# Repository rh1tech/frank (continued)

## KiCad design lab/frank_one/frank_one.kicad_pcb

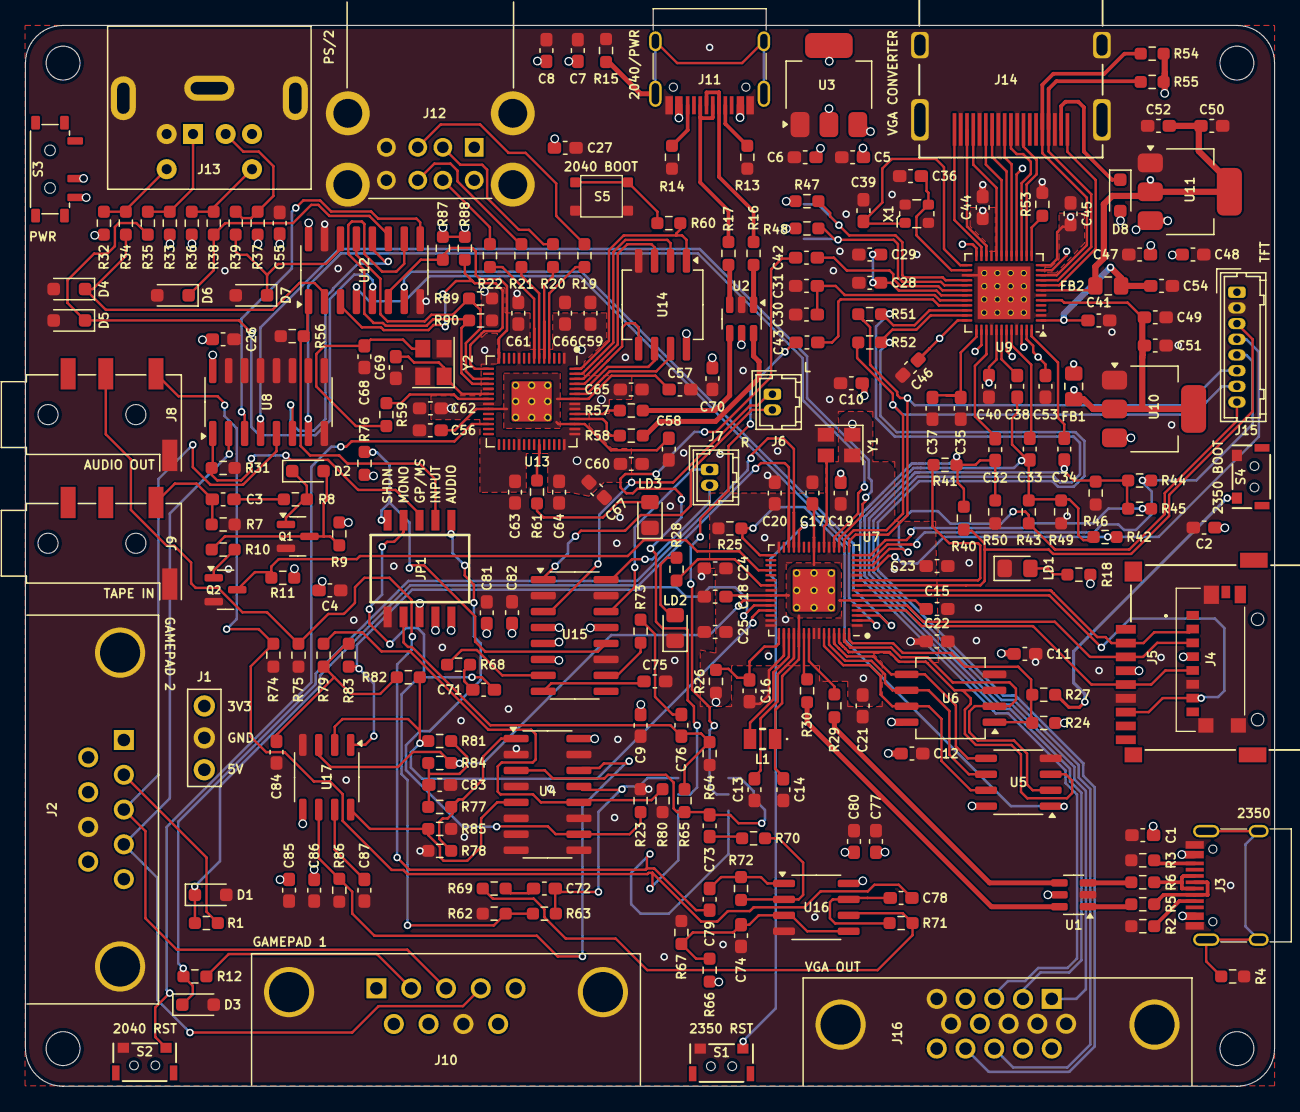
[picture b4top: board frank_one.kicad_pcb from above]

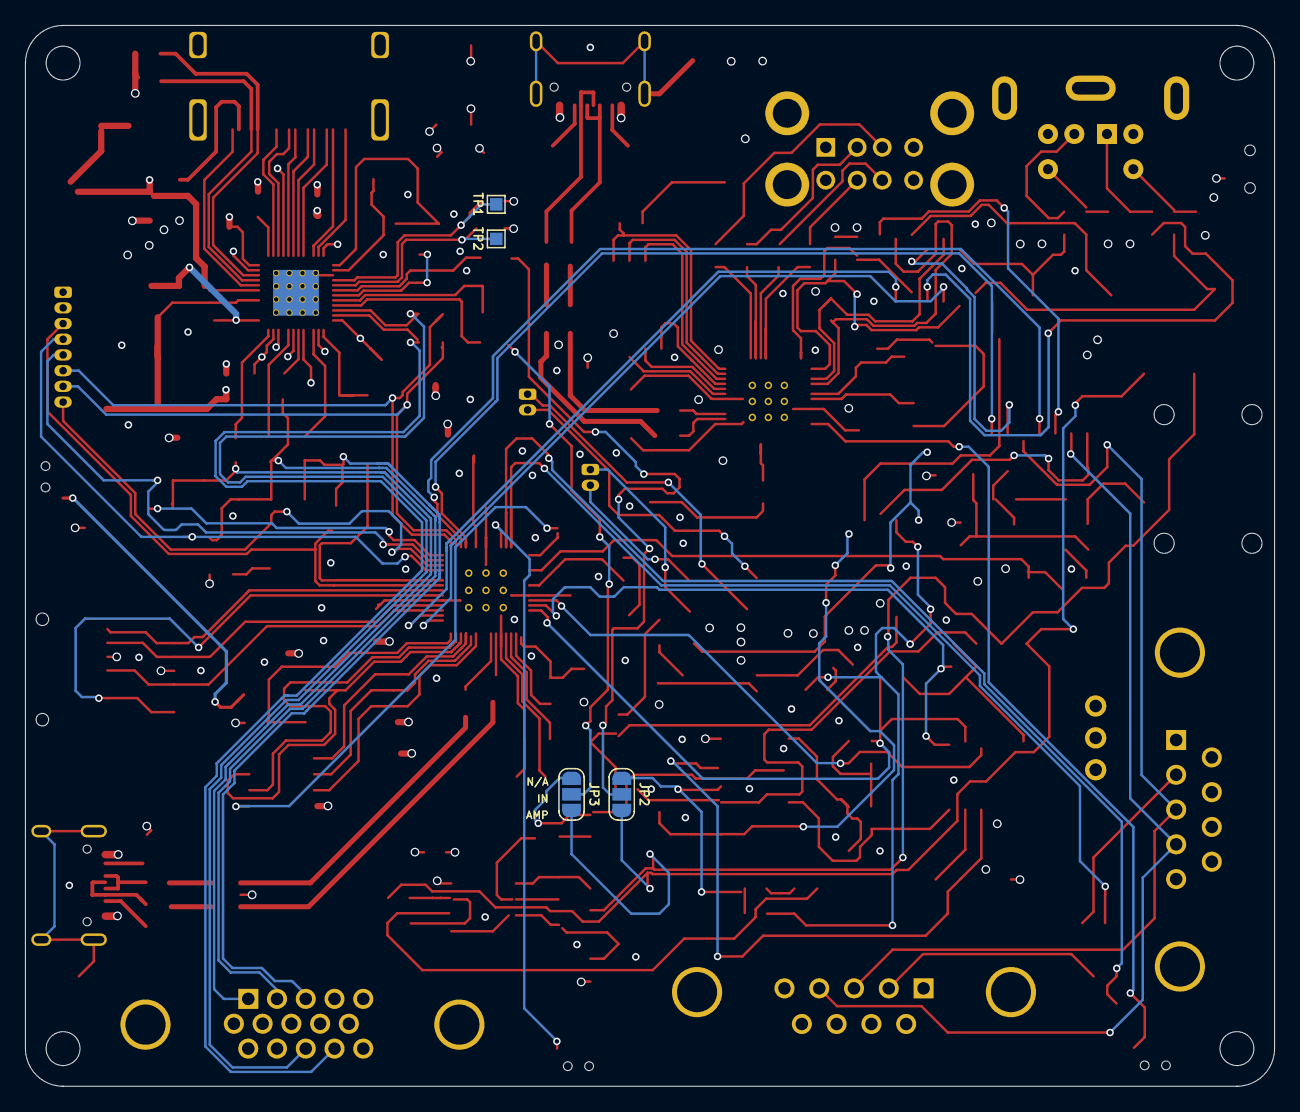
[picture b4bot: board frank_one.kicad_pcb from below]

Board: 4 copper layers, 99.5 x 84.5 mm, 243 parts (4 on the bottom side), 179 nets.

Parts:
C1, C5, C6, C7, C8, C47, C49, C50, C53, C54, C72, C73, C74, C77, C78, C79, C85, C87: 10u; Capacitor (0603)
C2, C3, C4, C9, C10, C11, C12, C15, C18, C19, C20, C21, C22, C23, C24, C25, C26, C27, C32, C33, C34, C40, C41, C44, C45, C46, C48, C55, C56, C57, C59, C61, C62, C63, C64, C65, C66, C67, C70, C75, C80, C86: 100n; Capacitor (0603)
C13, C14, C16, C17, C29, C31, C37: 4.7u; Capacitor (0603)
C28, C30, C35: 220n; Capacitor (0603)
C36, C39, C68, C69: 15p; Capacitor (0603)
C38: 1n; Capacitor (0603)
C42, C43, C51, C52, C58, C60, C71, C76, C81: 1u; Capacitor (0603)
C82: 47u; Capacitor (0603)
C83, C84: 47n; Capacitor (0603)
D1, D3, D4, D5, D6, D7: 3V3; Diode (SOD-323)
D2: 1N4148; Diode (SOD-323)
D8: 1N5819WS; Diode (SOD-323)
FB1, FB2: 220R; Inductor (0805)
H1, H2, H3, H4: MountingHole; Mounting Hole (2.7mm)
J1: PWR; Pin Header (1x03)
J2, J10: D-SUB 9 Male; D-SUB (9 pin, male, top mount)
J3, J11: USB4215-03-A; USB Type C
J4: 0475710001; MicroSD (SMD, short)
J5: 104031-0811; MicroSD (SMD, long)
J6: PAM L; Connector Female 1.25 JST 2P
J7: PAM R; Connector Female 1.25 JST 2P
J8, J9: PJ-320D; Jack (3.5mm, PJ-320D)
J12: SS-52100-004; USB Type A (stacked)
J13: MDC-036; MiniDIN (6 Pin, female)
J14: DC3RX19JA2; HDMI (female)
J15: Pin Header 1x08; Connector Female 1.25 JST 8P
J16: D-SUB 15 Female; D-SUB (15 pin, female)
JP1: Main Jumpers; SMD Switch (5P)
JP2: VGA AUDIO L; Jumper (solder, 3 pins)
JP3: VGA AUDIO R; Jumper (solder, 3 pins)
L1: 3.3u; Inductor (0806)
LD1: Power; LED (0805)
LD2, LD3: Blue; LED (0805)
Q1, Q2: BC850; SOT-23
R1, R11, R12, R18, R27, R28, R32, R33, R36, R37, R53, R59, R60, R61, R83, R84: 1K; Resistor (0603)
R2, R3, R13, R14: 5.1K; Resistor (0603)
R4, R15: 1M; Resistor (0603)
R5, R6, R16, R17, R19, R20, R21, R22: 22R; Resistor (0603)
R7, R34, R35, R38, R39, R51, R52: 100R; Resistor (0603)
R8, R9, R10, R23, R24, R25, R31, R56, R63, R65, R66, R67, R68, R69, R70, R73, R76, R77, R79, R87, R88, R89, R90: 10K; Resistor (0603)
R26: 33R; Resistor (0603)
R29, R30, R57, R58: 27R; Resistor (0603)
R40, R42, R44: 800R; Resistor (0603)
R41, R43, R45: 400R; Resistor (0603)
R46, R49, R50: 75R; Resistor (0603)
R47, R48: 4.7K; Resistor (0603)
R54, R55, R62, R64, R78, R80, R81, R82: 2K; Resistor (0603)
R71, R72: 47K; Resistor (0603)
R74, R75: 20K; Resistor (0603)
R85, R86: 470R; Resistor (0603)
S1, S2: Reset; TACT-SIDE-4623
S3: MSK12C02; Switch (MSK12C02)
S4: TS-1233; TACT-SIDE-4623
S5: Boot 2040; Button (SMD, 3x3mm, 1-1)
TP1: MS9288_SCL; TestPoint (Pad 1.0x1.0mm)
TP2: MS9288_SDA; TestPoint (Pad 1.0x1.0mm)
U1, U2: USBLC6-2SC6; SOT-23-6
U3: NCP1117 3.3; SOT-223
U4: 74HC4052D; SOP-16
U5: ESP-PSRAM32; SO-8
U6: W25Q128JVS; SOIC-8
U7: RP2350; QFN 60 (RP2350A)
U8, U12: SN74CBT3257CDR; SOP-16
U9: MS9288A; QFN 48
U10: AMS1117-3.3; SOT-223
U11: AMS1117-1.8; SOT-223
U13: RP2040; QFN 56
U14: W25Q128JVSIQ; SOIC-8
U15: PAM8403D; SOP-16
U16: LM358; SO-8
U17: TDA1387T; SO-8
X1: 24.576 MHz; Crystal (2520)
Y1: ASE-12MHz; Crystal (3225, active)
Y2: 12 MHz; Crystal (3225)

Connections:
+1V1: C14.1, C15.1, C17.1, C18.1, L1.1, U7.6 (DVDD), U7.23 (DVDD), U7.39 (DVDD), U7.50 (VREG_FB)
+3V3: C2.2, C4.1, C6.1, C9.2, C10.1, C11.1, C12.1, C13.1, C19.1, C20.1, C21.1, C22.1, C23.1, C24.1, C25.1, C59.1, C60.1, C61.1, C62.1, C63.1, C64.1, C65.1, C66.1, C67.1, C70.1, J1.1, J4.P4 (VDD), J5.4 (VDD), R9.1, R11.1, R18.2, R24.1, R25.2, R26.1, R87.2, R88.2, R89.2, R90.2, U3.2 (VO), U4.16 (VCC), U5.8 (VCC), U6.8 (VCC), U7.1 (IOVDD), U7.11 (IOVDD), U7.20 (IOVDD), U7.30 (IOVDD), U7.38 (IOVDD), U7.44 (ADC_AVDD), U7.45 (IOVDD), U7.49 (VREG_VIN), U7.53 (USB_OTP_VDD), U7.54 (QSPI_IOVDD), U13.1 (IOVDD), U13.10 (IOVDD), U13.22 (IOVDD), U13.33 (IOVDD), U13.42 (IOVDD), U13.43 (ADC_AVDD), U13.44 (VREG_IN), U13.48 (USB_VDD), U13.49 (IOVDD), U14.8 (VCC), Y1.1 (EN), Y1.4 (Vdd)
/AMP_IN_L: C72.1, JP2.1, R63.1, U4.13 (1Z)
/AMP_IN_R: C73.1, JP3.1, R65.1, U4.3 (2Z)
/AMP_OUT_L: C78.2, J8.T, JP2.3, R74.2
/AMP_OUT_R: C79.2, J8.R, JP3.3, R75.2
/ASW: JP1.1, R23.2, U4.10 (S0)
/Audio Out/AMP_PAM_OUTL_M: J6.2, U15.3 (-OUTL)
/Audio Out/AMP_PAM_OUTL_P: J6.1, U15.1 (+OUT_L)
/Audio Out/AMP_PAM_OUTR_M: J7.2, U15.14 (-OUT_R)
/Audio Out/AMP_PAM_OUTR_P: J7.1, U15.16 (+OUT_R)
/GP_J3: J2.3, J10.3, U8.5 (2B1)
/GP_J4: J2.4, J10.4, U8.2 (1B1)
/MONO_L: C71.1, JP1.4, R62.1, R63.2
/MONO_R: C76.1, JP1.7, R64.1, R65.2
/MSW: JP1.3, R31.2, U8.1 (S)
/MS_CLK: U8.3 (1B2), U12.9 (3A)
/MS_DATA: U8.6 (2B2), U12.12 (4A)
/PS2/PS2_KB_CLK: J13.5, R32.1, R34.1
/PS2/PS2_KB_DATA: J13.1, R33.1, R35.1
/PS2/PS2_MS_CLK: J13.6, R36.1, R38.1
/PS2/PS2_MS_DATA: J13.2, R37.1, R39.1
/PS2_K_CLK: D4.1 (K), R34.2, U12.2 (1B1)
/PS2_K_DATA: D5.1 (K), R35.2, U12.5 (2B1)
/PS2_M_CLK: D6.1 (K), R38.2, U12.11 (3B1)
/PS2_M_DATA: D7.1 (K), R39.2, U12.14 (4B1)
/PSW: JP1.2, R56.2, U12.1 (S)
/PWM_OUT_L: R79.2, R80.1, U4.12 (1Y0)
/PWM_OUT_R: R77.2, R78.1, U4.1 (2Y0)
/RP1_D+: R29.1, U1.4 (I/O2)
/RP1_D-: R30.1, U1.6 (I/O1)
/RP1_GPIO0: U7.2 (GPIO0), U12.4 (1A)
/RP1_GPIO1: U7.3 (GPIO1), U12.7 (2A)
/RP1_GPIO2: J4.P5 (CLK), J5.5 (CLK), U7.4 (GPIO2)
/RP1_GPIO3: J4.P3 (CMD), J5.3 (CMD), U7.5 (GPIO3)
/RP1_GPIO4: J4.P7 (DAT0), J5.7 (DAT0), U7.7 (GPIO4)
/RP1_GPIO5: J4.P2 (CD/DAT3), J5.2 (DAT3/CD), U7.8 (GPIO5)
/RP1_GPIO6: J15.3, R40.1, U7.9 (GPIO6)
/RP1_GPIO7: R41.1, U7.10 (GPIO7)
/RP1_GPIO8: J15.4, R42.1, U7.12 (GPIO8)
/RP1_GPIO9: J15.8, R43.1, U7.13 (GPIO9)
/RP1_GPIO10: J15.5, R44.1, U7.14 (GPIO10)
/RP1_GPIO11: R45.1, U7.15 (GPIO11)
/RP1_GPIO12: J15.6, R51.1, U7.16 (GPIO12)
/RP1_GPIO13: J15.7, R52.1, U7.17 (GPIO13)
/RP1_GPIO14: U7.18 (GPIO14), U8.4 (1A)
/RP1_GPIO15: U7.19 (GPIO15), U8.7 (2A)
/RP1_GPIO16: D3.1 (K), R12.1, U7.27 (GPIO16)
/RP1_GPIO17: D1.1 (K), R1.1, U7.28 (GPIO17)
/RP1_GPIO19: R25.1, U5.1 (~CE), U7.31 (GPIO19)
/RP1_GPIO22: Q2.3 (C), R11.2, U7.34 (GPIO22)
/RP1_GPIO26: R84.2, U7.40 (GPIO26_ADC0), U17.3 (DATA)
/RP1_GPIO27: R83.2, U7.41 (GPIO27_ADC1), U17.1 (SCLK)
/RP1_GPIO28: R81.1, R82.1, U7.42 (GPIO28_ADC2), U17.2 (LRCK)
/RP1_RUN: S1.1, U7.26 (RUN)
/RP2_D+: R57.1, U2.4 (I/O2)
/RP2_D-: R58.1, U2.6 (I/O1)
/RP2_GPIO2: R19.1, U13.4 (GPIO2)
/RP2_GPIO3: R20.1, U13.5 (GPIO3)
/RP2_GPIO4: R21.1, U13.6 (GPIO4)
/RP2_GPIO5: R22.1, U13.7 (GPIO5)
/RP2_GPIO11: R87.1, U12.6 (2B2), U13.14 (GPIO11)
/RP2_GPIO12: R88.1, U12.3 (1B2), U13.15 (GPIO12)
/RP2_GPIO14: R89.1, U12.13 (4B2), U13.17 (GPIO14)
/RP2_GPIO15: R90.1, U12.10 (3B2), U13.18 (GPIO15)
/RP2_RUN: S2.1, U13.26 (RUN)
/RP2040/GPIO25: R61.2, U13.37 (GPIO25)
/RP2040/QSPI_SCLK: U13.52 (QSPI_SCLK), U14.6 (CLK)
/RP2040/QSPI_SD0: U13.53 (QSPI_SD0), U14.5 (DI(IO0))
/RP2040/QSPI_SD1: U13.55 (QSPI_SD1), U14.2 (DO(IO1))
/RP2040/QSPI_SD2: U13.54 (QSPI_SD2), U14.3 (IO2)
/RP2040/QSPI_SD3: U13.51 (QSPI_SD3), U14.7 (IO3)
/RP2040/QSPI_SS: R60.1, U13.56 (QSPI_SS), U14.1 (~CS)
/RP2040/XIN: C69.1, U13.20 (XIN), Y2.1
/RP2040/XOUT: R59.1, U13.21 (XOUT)
/RP2350A/QSPI_SCLK: U5.6 (SCLK), U6.6 (CLK), U7.56 (QSPI_SCLK)
/RP2350A/QSPI_SD0: U5.5 (SI/SIO), U6.5 (DI(IO0)), U7.57 (QSPI_SD0)
/RP2350A/QSPI_SD1: U5.2 (SO/SIO), U6.2 (DO(IO1)), U7.59 (QSPI_SD1)
/RP2350A/QSPI_SD2: U5.3 (SIO2), U6.3 (IO2), U7.58 (QSPI_SD2)
/RP2350A/QSPI_SD3: U5.7 (SIO3), U6.7 (IO3), U7.55 (QSPI_SD3)
/RP2350A/QSPI_SS: R24.2, R27.1, U6.1 (~CS), U7.60 (QSPI_SS)
/RP2350A/VREG_AVDD: C16.1, R26.2, U7.46 (VREG_AVDD)
/RP2350A/VREG_LX: L1.2, U7.48 (VREG_LX)
/RP2350A/XIN: U7.21 (XIN), Y1.3 (OUT)
/RP2350A/~USB_BOOT: R27.2, S4.2
/SHND: JP1.5, R76.2, U15.12 (SHND)
/TDA_L: R86.2, U4.14 (1Y1), U17.6 (A_LEFT)
/TDA_R: R85.1, U4.5 (2Y1), U17.8 (A_RIGHT)
/VGA/ALIN: C42.1, U9.30 (ALIN)
/VGA/AMS_1V8: C44.1, C50.1, C52.1, FB2.1, U9.7 (AVDD18), U9.16 (AVDD18), U9.21 (AVDD18), U11.2 (VO)
/VGA/AMS_1V8A: C40.1, C41.1, C54.1, FB2.2, U9.1 (AVDD18_ADC), U9.41 (AVDD18_ADC), U9.46 (AVDD18_ADC)
/VGA/AMS_3V3: C46.1, C49.1, C51.1, FB1.2, U9.5 (DVDD33), U9.11 (DVDD33), U9.24 (DVDD33), U9.36 (DVDD33), U10.2 (VO)
/VGA/AMS_3V3A: C45.1, C53.1, FB1.1, U9.12 (AVDD33), U9.38 (AVDD33), U9.43 (AVDD33), U9.47 (AVDD33)
/VGA/ARIN: C43.1, U9.33 (ARIN)
/VGA/B: C32.1, U9.39 (B/Pb)
/VGA/DCCSCL: J14.15 (SCL), R54.1, U9.10 (DCCSCL)
/VGA/DDCSDA: J14.16 (SDA), R55.1, U9.9 (DDCSDA)
/VGA/G: C33.1, U9.44 (G/Y)
/VGA/HPDT: J14.19 (HOT_PLUG_DET), U9.8 (HotPlugDetect)
/VGA/HS: J16.13, R51.2, U9.34 (HSIN)
/VGA/R: C34.1, U9.48 (R/Pr)
/VGA/SCL: R47.1, TP1.1, U9.28 (SCL)
/VGA/SDA: R48.1, TP2.1, U9.29 (SDA)
/VGA/SOG_B: C32.2, J16.3, R40.2, R41.2, R50.1
/VGA/SOG_G: C33.2, C38.2, J16.2, R42.2, R43.2, R49.1
/VGA/SOG_R: C34.2, J16.1, R44.2, R45.2, R46.1
/VGA/TMDS_CLK+: J14.10 (CLKP), U9.15 (TMDS_CLK+)
/VGA/TMDS_CLK-: J14.12 (CLKN), U9.14 (TMDS_CLK-)
/VGA/TMDS_D0+: J14.7 (D0P), U9.18 (TMDS-D0+)
/VGA/TMDS_D0-: J14.9 (D0N), U9.17 (TMDS_D0-)
/VGA/TMDS_D1+: J14.4 (D1P), U9.20 (TMDS_D1+)
/VGA/TMDS_D1-: J14.6 (D1N), U9.19 (TMDS_D1-)
/VGA/TMDS_D2+: J14.1 (D2P), U9.23 (TMDS_D2+)
/VGA/TMDS_D2-: J14.3 (D2N), U9.22 (TMDS_D2-)
/VGA/VS: J16.14, R52.2, U9.35 (VSIN)
/VGA_AIN_L: C42.2, JP2.2
/VGA_AIN_R: C43.2, JP3.2
GND: C1.2, C2.1, C4.2, C5.2, C6.2, C7.2, C8.2, C9.1, C10.2, C11.2, C12.2, C13.2, C14.2, C15.2, C16.2, C17.2, C18.2, C19.2, C20.2, C21.2, C22.2, C23.2, C24.2, C25.2, C26.1, C27.2, C28.2, C29.2, C30.2, C31.2, C35.2, C36.2, C37.2, C39.2, C40.2, C41.2, C44.2, C45.2, C46.2, C47.2, C48.2, C49.2, C50.2, C51.2, C52.2, C53.2, C54.2, C55.1, C56.2, C57.2, C58.2, C59.2, C60.2, C61.2, C62.2, C63.2, C64.2, C65.2, C66.2, C67.2, C68.2, C69.2, C70.2, C74.1, C75.2, C77.1, C80.1, C81.2, C82.2, C83.2, C84.2, C85.2, C86.2, C87.2, D1.2 (A), D3.2 (A), D4.2 (A), D5.2 (A), D6.2 (A), D7.2 (A), J1.2, J2.8, J3.1 (GND), J3.12 (GND), J4.G1 (GND_1), J4.G2 (GND_2), J4.G3 (GND_3), J4.P6 (VSS), J5.6 (VSS), J8.S, J9.S, J10.8, J11.1 (GND), J11.12 (GND), J12.4 (GND1), J12.8 (GND2), J12.9 (Shield), J13.3, J14.2 (G_D2), J14.5 (G_D1), J14.8 (G_D0), J14.11 (G_CLK), J14.17 (G_DDC/CEC), J14.20 (SHIELD1), J14.21 (SHIELD2), J14.22 (SHIELD3), J14.23 (SHIELD4), J15.1, J16.0, J16.5, J16.6, J16.7, J16.8, J16.10, JP1.6, LD1.1 (K), LD2.1 (K), LD3.1 (K), Q1.2 (E), Q2.2 (E), R2.1, R3.1, R4.2, R7.2, R13.1, R14.1, R15.2, R23.1, R31.1, R46.2, R49.2, R50.2, R53.1, R56.1, R62.2, R64.2, R67.1, R74.1, R75.1, R78.2, R80.2, R85.2, R86.1, S1.2, S2.2, S4.1, S5.2, U1.2 (GND), U2.2 (GND), U3.1 (GND), U4.2 (2Y2), U4.4 (2Y3), U4.6 (~E), U4.7 (VEE), U4.8 (GND), U4.9 (S1), U4.11 (1Y3), U4.15 (1Y2), U5.4 (VSS), U6.4 (GND), U7.47 (VREG_PGND), U7.61 (GND), U8.8 (GND), U8.9 (3A), U8.10 (3B2), U8.11 (3B1), U8.12 (4A), U8.13 (4B2), U8.14 (4B1), U8.15 (~OE), U9.2 (GND), U9.6 (GND), U9.27 (GND), U9.40 (GND), U9.45 (GND), U9.49 (EP), U10.1 (GND), U11.1 (GND), U12.8 (GND), U12.15 (~OE), U13.19 (TESTEN), U13.57 (GND), U14.4 (GND), U15.2 (PGND), U15.11 (GND), U15.15 (PGND), U16.4 (V-), U17.4 (AGND), X1.2 (GND), X1.4 (GND), Y1.2 (GND), Y2.2, Y2.4
GPIO25: R28.2, U7.37 (GPIO25)
unnamed: C3.1, J9.T, R7.1
unnamed: C3.2, R8.1
unnamed: C68.1, R59.2, Y2.3
unnamed: C71.2, R68.2
unnamed: C72.2, R69.2
unnamed: C73.2, R70.2
unnamed: C76.2, R73.2
unnamed: C78.1, R71.1, U16.7
unnamed: C79.1, R72.1, U16.1
unnamed: C83.1, R77.1, R81.2, R84.1
unnamed: C84.1, R79.1, R82.2, R83.1
unnamed: D2.2 (A), Q1.3 (C), R9.2, R10.1
unnamed: D2.1 (K), Q1.1 (B), R8.2
unnamed: D8.1 (K), J14.18 (+5V)
unnamed: J2.2, R1.2
unnamed: J3.4 (CC1), R2.2
unnamed: J3.10 (CC2), R3.2
unnamed: J3.5 (DN2), J3.7 (DN1), R5.2
unnamed: J3.6 (DP1), J3.8 (DP2), R6.2
unnamed: J3.13 (SHIELD), R4.1
unnamed: J10.2, R12.2
unnamed: J11.4 (CC1), R13.2
unnamed: J11.10 (CC2), R14.2
unnamed: J11.5 (DN2), J11.7 (DN1), R16.2
unnamed: J11.6 (DP1), J11.8 (DP2), R17.2
unnamed: J11.13 (SHIELD), R15.1
unnamed: J12.3 (D1+), R19.2
unnamed: J12.2 (D1-), R20.2
unnamed: J12.7 (D2+), R21.2
unnamed: J12.6 (D2-), R22.2
unnamed: LD1.2 (A), R18.1
unnamed: LD2.2 (A), R28.1
unnamed: LD3.2 (A), R61.1
unnamed: Q2.1 (B), R10.2
unnamed: R5.1, U1.1 (I/O1)
unnamed: R6.1, U1.3 (I/O2)
unnamed: R16.1, U2.1 (I/O1)
unnamed: R17.1, U2.3 (I/O2)
unnamed: R60.2, S5.1
unnamed: J11.2 (VBUS), J11.11 (VBUS), S3.2 (B)
unnamed: R30.2, U7.51 (USB_DM)
unnamed: R29.2, U7.52 (USB_DP)
unnamed: C35.1, C37.1, U9.37 (REFP)
unnamed: C28.1, C29.1, U9.31 (REFQ0)
unnamed: C30.1, C31.1, U9.32 (REFQ1)
unnamed: C38.1, U9.42 (SOG/Y)
unnamed: R53.2, U9.13 (SWREF1k)
unnamed: C39.1, U9.25 (XTI), X1.1 (OSC)
unnamed: C36.1, U9.26 (XTO), X1.3 (OSC)
unnamed: R58.2, U13.46 (USB_DM)
unnamed: R57.2, U13.47 (USB_DP)
unnamed: C56.1, C57.1, C58.1, U13.23 (DVDD), U13.45 (VREG_VOUT), U13.50 (DVDD)
unnamed: R68.1, U15.7 (INL)
unnamed: R73.1, U15.10 (INR)
unnamed: C75.1, U15.8 (VREF)
unnamed: C74.2, R66.1, R67.2, U16.3 (+), U16.5 (+)
unnamed: R70.1, R72.2, U16.2 (-)
unnamed: R69.1, R71.2, U16.6 (-)
unnamed: C87.1, U17.7 (FLT)
VBUS: C1.1, C5.1, C7.1, C8.1, C26.2, C27.1, C47.1, C48.1, C55.2, C77.2, C80.2, C81.1, C82.1, C85.1, C86.1, D8.2 (A), J1.3, J2.6, J3.2 (VBUS), J3.11 (VBUS), J10.6, J12.1 (VBUS1), J12.5 (VBUS2), J13.4, J15.2, JP1.8, JP1.9, JP1.10, R32.2, R33.2, R36.2, R37.2, R47.2, R48.2, R54.2, R55.2, R66.2, R76.1, S3.3 (A), U1.5 (VBUS), U2.5 (VBUS), U3.3 (VI), U8.16 (VCC), U10.3 (VI), U11.3 (VI), U12.16 (VCC), U15.4 (PVDD), U15.5 (MUTE), U15.6 (VDD), U15.13 (PVDD), U16.8 (V+), U17.5 (VA)

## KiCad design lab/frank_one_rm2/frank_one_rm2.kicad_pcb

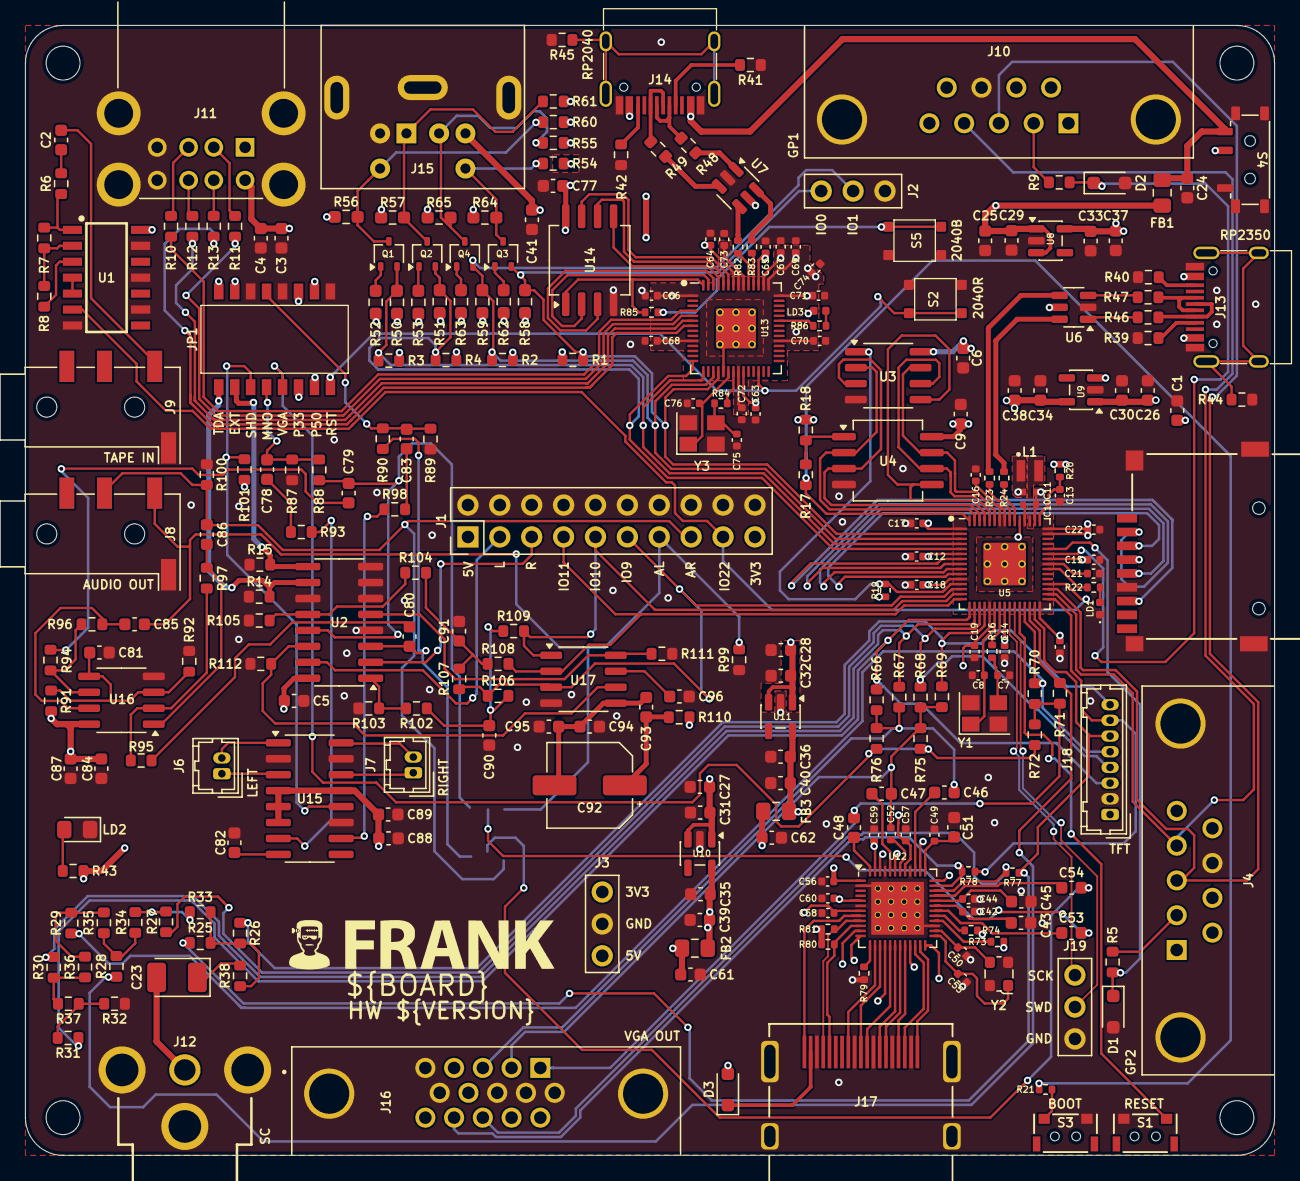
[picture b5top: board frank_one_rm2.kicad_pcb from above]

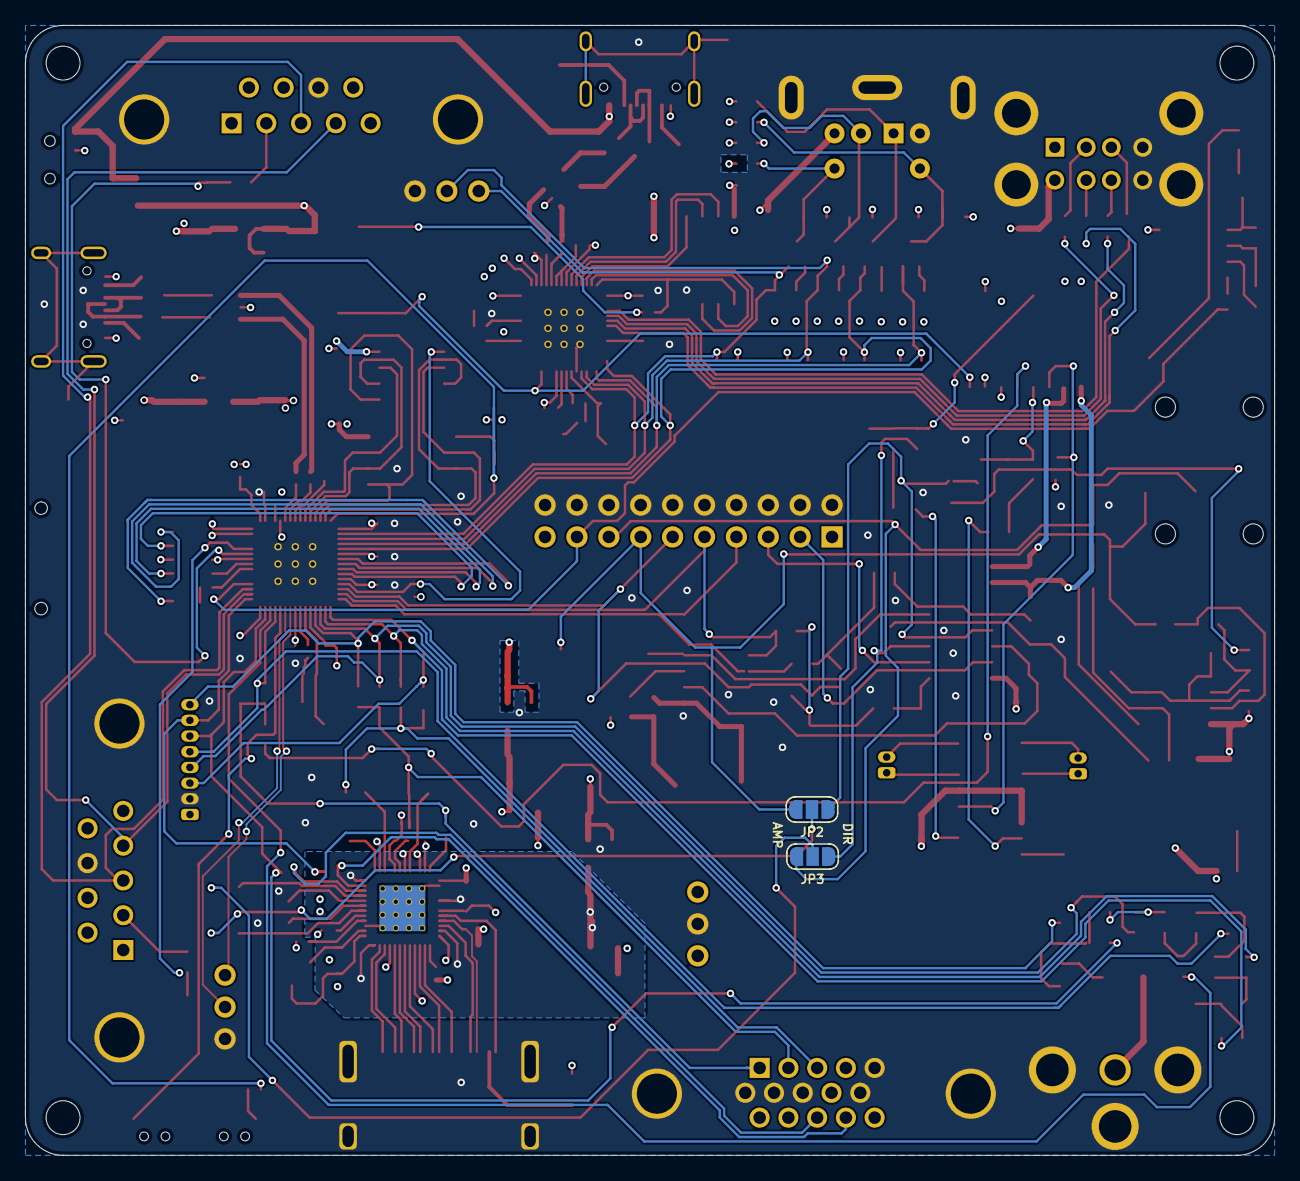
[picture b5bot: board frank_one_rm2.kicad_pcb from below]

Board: 4 copper layers, 99.5 x 90.0 mm, 273 parts (2 on the bottom side), 195 nets.

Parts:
C1, C2, C5, C6, C9, C24, C29, C30, C31, C32, C33, C34, C35, C36, C41, C46, C47, C48, C77, C82, C87, C95: 100n; Capacitor (0603, S)
C3, C4, C25, C26, C27, C28, C37, C38, C39, C40, C61, C62, C79, C80, C81, C84, C85, C86, C94, C96: 10u; Capacitor (0603, S)
C7, C8, C50, C55, C75, C76: 15p; Capacitor (0402, S)
C10, C11: 4.7u; Capacitor (0402, SP)
C12, C15, C16, C17, C18, C19, C20, C21, C22, C56, C57, C58, C59, C60, C63, C64, C66, C68, C69, C70, C71, C72, C73, C74: 100n; Capacitor (0402, S)
C13, C14: 4.7u; Capacitor (0402, S)
C23: 220u; Capacitor (3528, tantalum, polar)
C42, C44, C49: 220n; Capacitor (0402, S)
C43, C45, C51: 4.7u; Capacitor (0603, S)
C52: 1n; Capacitor (0402, S)
C53, C54, C78, C83, C88, C93: 1u; Capacitor (0603, S)
C65, C67: 1u; Capacitor (0402, S)
C89: 47u; Capacitor (0603, S)
C90, C91: 47n; Capacitor (0603, S)
C92: 100u; CP_Elec_6.3x5.4
D1, D2: 3V3; Diode (SOD-323)
D3: 1N5819WS; Diode (SOD-323)
FB1: 330R; Inductor (0805)
FB2, FB3: 220R; Inductor (0805)
H1, H2, H3, H4: MountingHole; Mounting Hole (2.7mm)
J1: EXT Sound; PinHeader_2x10_P2.54mm_Vertical
J2: UART; Pin Header (1x03)
J3: PWR; Pin Header (1x03)
J4, J10: D-SUB 9 Male; D-SUB (9 pin, male, top mount)
J5: 104031-0811; MicroSD (SMD, long)
J6: PAM L; Connector Female 1.25 JST 2P
J7: PAM R; Connector Female 1.25 JST 2P
J8, J9: PJ-320D; Jack (3.5mm, PJ-320D)
J11: SS-52100-004; USB Type A (stacked)
J12: RCA-103; RCJ-012
J13, J14: USB4215-03-A; USB Type C
J15: MDC-036; MiniDIN (6 Pin, female)
J16: D-SUB 15 Female; D-SUB (15 pin, female)
J17: DC3RX19JA2; HDMI (female)
J18: Pin Header 1x08; Connector Female 1.25 JST 8P
J19: DEBUG; Pin Header (1x03)
JP1: Main Jumpers; DS05127208BKSMTTR
JP2: VGA AUDIO L; Jumper (solder, 3 pins)
JP3: VGA AUDIO R; Jumper (solder, 3 pins)
L1: 3.3u; AOTA-B201610S3R3-101-T
LD1: Data; LED (0402, S)
LD2: Power; LED (0805)
LD3: Blue; LED (0402, S)
Q1, Q2, Q3, Q4: BSS138; SOT-323_SC-70
R1, R2, R3, R4, R6: 4.7K; Resistor (0603, S)
R5, R9, R43, R108, R109: 1K; Resistor (0603, S)
R7, R8: 100K; Resistor (0603, S)
R10, R11, R12, R13, R46, R47, R48, R49: 22R; Resistor (0603, S)
R14, R15, R18, R54, R55, R60, R61, R88, R90, R91, R92, R93, R94, R95, R98, R101, R102, R104: 10K; Resistor (0603, S)
R16, R21, R22, R79, R84, R85, R86: 1K; Resistor (0402, S)
R17: 0R; Resistor (0603, S)
R19: 10K; Resistor (0402, S)
R20: 33R; Resistor (0402, S)
R23, R24, R82, R83: 27R; Resistor (0402, S)
R25: 750R; Resistor (0603, S)
R26, R27, R28, R29, R30, R31: 270R; Resistor (0603, S)
R32: 300R; Resistor (0603, S)
R33, R34, R35, R36, R37: 150R; Resistor (0603, S)
R38: 51R; Resistor (0603, S)
R39, R40, R41, R42: 5.1K; Resistor (0603, S)
R44, R45: 1M; Resistor (0603, S)
R50, R51, R56, R57, R58, R59, R64, R65: 22K; Resistor (0603)
R52, R53, R62, R63: 4.7K; Resistor (0603)
R66, R68, R70: 800R; Resistor (0603, S)
R67, R69, R71: 400R; Resistor (0603, S)
R72, R75, R76: 75R; Resistor (0603, S)
R73, R74: 4.7K; Resistor (0402, S)
R77, R78: 100R; Resistor (0402, S)
R80, R81: 2K; Resistor (0402, S)
R87, R89, R103, R105, R106, R107: 2K; Resistor (0603, S)
R96, R97: 47K; Resistor (0603, S)
R99, R100: 20K; Resistor (0603, S)
R110: 33R; Resistor (0603, S)
R111, R112: 470R; Resistor (0603, S)
S1: Reset; TACT-SIDE-4623
S2: Reset; Button (SMD, 3x3mm, 1-1)
S3: TS-1233; TACT-SIDE-4623
S4: MSK12C02; Switch (MSK12C02)
S5: Boot 2040; Button (SMD, 3x3mm, 1-1)
U1: CD4069UBM; SOIC127P600X175-14N
U2: 74HC4052D; SOP-16
U3: ESP-PSRAM32; SO-8
U4: W25Q128JVS; SOIC-8
U5: RP2350; QFN 60 (RP2350A)
U6, U7: USBLC6-2SC6; SOT-23-6
U8, U9, U10: ME6211C33M5; SOT-23-5
U11: ME6211C18M5; SOT-23-5
U12: MS9288A; QFN 48
U13: RP2040; QFN 56
U14: W25Q128JVSIQ; SOIC-8
U15: PAM8403D; SOP-16
U16: LM358; SO-8
U17: TDA1387T; SO-8
Y1, Y3: 12 MHz; Crystal (3225)
Y2: 24.576 MHz; Crystal (2520)

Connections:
+1V1: C11.1, C12.1, C14.1, C15.1, L1.1, U5.6 (DVDD), U5.23 (DVDD), U5.39 (DVDD), U5.50 (VREG_FB)
+1V8: C36.1, C40.1, C58.1, FB3.1, U11.5 (V_{OUT}), U12.7 (AVDD18), U12.16 (AVDD18), U12.21 (AVDD18)
+3V3: C1.2, C33.1, C37.1, C66.1, C67.1, C68.1, C69.1, C70.1, C71.1, C72.1, C73.1, C74.1, C77.1, J1.19, J3.1, J5.4 (VDD), R43.2, R50.1, R51.1, R52.1, R53.1, R58.1, R59.1, R62.1, R63.1, U1.14 (VDD), U8.5 (V_{OUT}), U13.1 (IOVDD), U13.10 (IOVDD), U13.22 (IOVDD), U13.33 (IOVDD), U13.42 (IOVDD), U13.43 (ADC_AVDD), U13.44 (VREG_IN), U13.48 (USB_VDD), U13.49 (IOVDD), U14.8 (VCC)
+3V3_2350: C6.1, C9.1, C10.1, C16.1, C17.1, C18.1, C19.1, C20.1, C21.1, C22.1, C34.1, C38.1, JP1.11, R18.1, R19.2, R20.1, U3.8 (VCC), U4.8 (VCC), U5.1 (IOVDD), U5.11 (IOVDD), U5.20 (IOVDD), U5.30 (IOVDD), U5.38 (IOVDD), U5.44 (ADC_AVDD), U5.45 (IOVDD), U5.49 (VREG_VIN), U5.53 (USB_OTP_VDD), U5.54 (QSPI_IOVDD), U9.5 (V_{OUT})
+3V3_VIDEO: C35.1, C39.1, C60.1, FB2.2, U10.5 (V_{OUT}), U12.5 (DVDD33), U12.11 (DVDD33), U12.24 (DVDD33), U12.36 (DVDD33)
/AMP_IN_L: C79.1, JP2.1, R88.1, U2.13 (1Z)
/AMP_IN_R: C80.1, JP3.1, R90.1, U2.3 (2Z)
/AMP_OUT_L: C85.2, J1.13, J8.T, JP2.3, R99.2
/AMP_OUT_R: C86.2, J1.15, J8.R, JP3.3, R100.2
/Audio Out/AMP_PAM_OUTL_M: J6.2, U15.3 (-OUTL)
/Audio Out/AMP_PAM_OUTL_P: J6.1, U15.1 (+OUT_L)
/Audio Out/AMP_PAM_OUTR_M: J7.2, U15.14 (-OUT_R)
/Audio Out/AMP_PAM_OUTR_P: J7.1, U15.16 (+OUT_R)
/Composite/CVBS: C23.2, J12.1
/EXT_L: J1.3, U2.15 (1Y2)
/EXT_R: J1.5, U2.2 (2Y2)
/J_EXT: JP1.2, R15.2, U2.9 (S1)
/J_TDA: JP1.1, R14.2, U2.10 (S0)
/MONO_L: C78.1, JP1.4, R87.1, R88.2
/MONO_R: C83.1, JP1.13, R89.1, R90.2
/PS2/KB_CLK_5V: J15.5, Q1.3 (D), R56.2, R60.1
/PS2/KB_DATA_5V: J15.1, Q2.3 (D), R57.2, R61.1
/PS2/MS_CLK_5V: J15.6, Q3.3 (D), R54.1, R64.2
/PS2/MS_DATA_5V: J15.2, Q4.3 (D), R55.1, R65.2
/PUP3V3: JP1.6, R1.2, R2.2, R3.2, R4.2
/PUP5V: JP1.7, R54.2, R55.2, R60.2, R61.2
/PWM_OUT_L: R104.2, R105.1, U2.12 (1Y0)
/PWM_OUT_R: R102.2, R103.1, U2.1 (2Y0)
/Power/VBUS_IN: C24.1, FB1.2, J14.2 (VBUS), J14.11 (VBUS), S4.3 (A)
/RP1_D+: R23.1, U6.4 (I/O2)
/RP1_D-: R24.1, U6.6 (I/O1)
/RP1_GPIO0: J2.1, Q3.2 (S), R1.1, R58.2, U5.2 (GPIO0), U13.18 (GPIO15)
/RP1_GPIO1: J2.2, Q4.2 (S), R2.1, R59.2, U5.3 (GPIO1), U13.17 (GPIO14)
/RP1_GPIO2: Q1.2 (S), R3.1, R50.2, U5.4 (GPIO2), U13.15 (GPIO12)
/RP1_GPIO3: Q2.2 (S), R4.1, R51.2, U5.5 (GPIO3), U13.14 (GPIO11)
/RP1_GPIO4: J5.7 (DAT0), U5.7 (GPIO4)
/RP1_GPIO5: J5.2 (DAT3/CD), U5.8 (GPIO5)
/RP1_GPIO6: J5.5 (CLK), U5.9 (GPIO6)
/RP1_GPIO7: J5.3 (CMD), U5.10 (GPIO7)
/RP1_GPIO8: R19.1, U3.1 (~CE), U5.12 (GPIO8)
/RP1_GPIO9: J1.11, R106.1, R107.1, U5.13 (GPIO9), U17.3 (DATA)
/RP1_GPIO10: J1.9, R109.2, U5.14 (GPIO10), U17.1 (SCLK)
/RP1_GPIO11: J1.7, R108.2, U5.15 (GPIO11), U17.2 (LRCK)
/RP1_GPIO12: J18.3, R31.1, R66.1, U5.16 (GPIO12)
/RP1_GPIO13: R30.1, R67.1, U5.17 (GPIO13)
/RP1_GPIO14: J18.4, R27.1, R68.1, U5.18 (GPIO14)
/RP1_GPIO15: J18.8, R26.1, R69.1, U5.19 (GPIO15)
/RP1_GPIO16: J18.5, R29.1, R70.1, U5.27 (GPIO16)
/RP1_GPIO17: R28.1, R71.1, U5.28 (GPIO17)
/RP1_GPIO18: J18.6, R25.1, R77.1, U5.29 (GPIO18)
/RP1_GPIO19: J18.7, R78.1, U5.31 (GPIO19)
/RP1_GPIO20: J4.4, J10.4, U5.32 (GPIO20)
/RP1_GPIO21: J4.3, J10.3, U5.33 (GPIO21)
/RP1_GPIO22: J1.17, U1.6 (I=*C), U5.34 (GPIO22)
/RP1_GPIO26: D2.1 (K), R9.1, U5.40 (GPIO26_ADC0)
/RP1_GPIO27: D1.1 (K), R5.1, U5.41 (GPIO27_ADC1)
/RP1_RUN: S1.1, U5.26 (RUN)
/RP1_SWCLK: J19.1, U5.24 (SWCLK)
/RP1_SWD: J19.2, U5.25 (SWD)
/RP2_D+: R82.1, U7.4 (I/O2)
/RP2_D-: R83.1, U7.6 (I/O1)
/RP2_GPIO2: R10.1, U13.4 (GPIO2)
/RP2_GPIO3: R11.1, U13.5 (GPIO3)
/RP2_GPIO4: R12.1, U13.6 (GPIO4)
/RP2_GPIO5: R13.1, U13.7 (GPIO5)
/RP2_RUN: JP1.8, S2.1, U13.26 (RUN)
/RP2040/GPIO25: R86.2, U13.37 (GPIO25)
/RP2040/QSPI_SCLK: U13.52 (QSPI_SCLK), U14.6 (CLK)
/RP2040/QSPI_SD0: U13.53 (QSPI_SD0), U14.5 (DI(IO0))
/RP2040/QSPI_SD1: U13.55 (QSPI_SD1), U14.2 (DO(IO1))
/RP2040/QSPI_SD2: U13.54 (QSPI_SD2), U14.3 (IO2)
/RP2040/QSPI_SD3: U13.51 (QSPI_SD3), U14.7 (IO3)
/RP2040/QSPI_SS: R85.1, U13.56 (QSPI_SS), U14.1 (~CS)
/RP2040/XIN: C76.1, U13.20 (XIN), Y3.1
/RP2040/XOUT: R84.1, U13.21 (XOUT)
/RP2350A/QSPI_SCLK: U3.6 (SCLK), U4.6 (CLK), U5.56 (QSPI_SCLK)
/RP2350A/QSPI_SD0: U3.5 (SI/SIO), U4.5 (DI(IO0)), U5.57 (QSPI_SD0)
/RP2350A/QSPI_SD1: U3.2 (SO/SIO), U4.2 (DO(IO1)), U5.59 (QSPI_SD1)
/RP2350A/QSPI_SD2: U3.3 (SIO2), U4.3 (IO2), U5.58 (QSPI_SD2)
/RP2350A/QSPI_SD3: U3.7 (SIO3), U4.7 (IO3), U5.55 (QSPI_SD3)
/RP2350A/QSPI_SS: R17.2, R21.1, U5.60 (QSPI_SS)
/RP2350A/VREG_AVDD: C13.1, R20.2, U5.46 (VREG_AVDD)
/RP2350A/VREG_LX: L1.2, U5.48 (VREG_LX)
/RP2350A/XIN: C8.1, U5.21 (XIN), Y1.1
/RP2350A/XOUT: R16.1, U5.22 (XOUT)
/RP2350A/~USB_BOOT: R21.2, S3.2
/SHND: JP1.3, R101.2, U15.12 (SHND)
/TDA_L: R112.2, U2.14 (1Y1), U17.6 (A_LEFT)
/TDA_R: R111.1, U2.5 (2Y1), U17.8 (A_RIGHT)
/Tape In/TAPE: C2.2, J9.T
/VGA/ALIN: C53.1, U12.30 (ALIN)
/VGA/AMS_1V8A: C56.1, C57.1, C62.1, FB3.2, U12.1 (AVDD18_ADC), U12.41 (AVDD18_ADC), U12.46 (AVDD18_ADC)
/VGA/AMS_3V3A: C59.1, C61.1, FB2.1, U12.12 (AVDD33), U12.38 (AVDD33), U12.43 (AVDD33), U12.47 (AVDD33)
/VGA/ARIN: C54.1, U12.33 (ARIN)
/VGA/B: C46.1, U12.39 (B/Pb)
/VGA/DCCSCL: J17.15 (SCL), R80.1, U12.10 (DCCSCL)
/VGA/DDCSDA: J17.16 (SDA), R81.1, U12.9 (DDCSDA)
/VGA/G: C47.1, U12.44 (G/Y)
/VGA/HPDT: J17.19 (HOT_PLUG_DET), U12.8 (HotPlugDetect)
/VGA/HS: J16.13, R77.2, U12.34 (HSIN)
/VGA/R: C48.1, U12.48 (R/Pr)
/VGA/SCL: R73.1, U12.28 (SCL)
/VGA/SDA: R74.1, U12.29 (SDA)
/VGA/SOG_B: C46.2, J16.3, R66.2, R67.2, R76.1
/VGA/SOG_G: C47.2, C52.2, J16.2, R68.2, R69.2, R75.1
/VGA/SOG_R: C48.2, J16.1, R70.2, R71.2, R72.1
/VGA/TMDS_CLK+: J17.10 (CLKP), U12.15 (TMDS_CLK+)
/VGA/TMDS_CLK-: J17.12 (CLKN), U12.14 (TMDS_CLK-)
/VGA/TMDS_D0+: J17.7 (D0P), U12.18 (TMDS-D0+)
/VGA/TMDS_D0-: J17.9 (D0N), U12.17 (TMDS_D0-)
/VGA/TMDS_D1+: J17.4 (D1P), U12.20 (TMDS_D1+)
/VGA/TMDS_D1-: J17.6 (D1N), U12.19 (TMDS_D1-)
/VGA/TMDS_D2+: J17.1 (D2P), U12.23 (TMDS_D2+)
/VGA/TMDS_D2-: J17.3 (D2N), U12.22 (TMDS_D2-)
/VGA/VS: J16.14, R78.2, U12.35 (VSIN)
/VGA_AIN_L: C53.2, JP2.2
/VGA_AIN_R: C54.2, JP3.2
/VGA_BR: JP1.5, R72.2, R75.2, R76.2
GND: C1.1, C3.2, C4.2, C5.1, C6.2, C7.2, C8.2, C9.2, C10.2, C11.2, C12.2, C13.2, C14.2, C15.2, C16.2, C17.2, C18.2, C19.2, C20.2, C21.2, C22.2, C24.2, C25.1, C26.1, C27.1, C28.1, C29.1, C30.1, C31.1, C32.1, C33.2, C34.2, C35.2, C36.2, C37.2, C38.2, C39.2, C40.2, C41.2, C42.2, C43.2, C44.2, C45.2, C49.2, C50.2, C51.2, C55.2, C56.2, C57.2, C58.2, C59.2, C60.2, C61.2, C62.2, C63.2, C64.2, C65.2, C66.2, C67.2, C68.2, C69.2, C70.2, C71.2, C72.2, C73.2, C74.2, C75.2, C76.2, C77.2, C81.1, C82.2, C84.1, C87.1, C88.2, C89.2, C90.2, C91.2, C94.2, C95.2, C96.2, D1.2 (A), D2.2 (A), J1.2, J1.4, J1.6, J1.8, J1.10, J1.12, J1.14, J1.16, J1.18, J1.20, J2.3, J3.2, J4.8, J5.6 (VSS), J8.S, J9.S, J10.8, J11.4 (GND1), J11.8 (GND2), J11.9 (Shield), J12.2, J13.1 (GND), J13.12 (GND), J14.1 (GND), J14.12 (GND), J15.3, J16.0, J16.5, J16.6, J16.7, J16.8, J16.10, J17.2 (G_D2), J17.5 (G_D1), J17.8 (G_D0), J17.11 (G_CLK), J17.17 (G_DDC/CEC), J17.20 (SHIELD1), J17.21 (SHIELD2), J17.22 (SHIELD3), J17.23 (SHIELD4), J18.1, J19.3, JP1.9, JP1.12, JP1.14, LD1.1 (K), LD2.1 (K), LD3.1 (K), R14.1, R15.1, R32.1, R39.1, R40.1, R41.1, R42.1, R44.2, R45.2, R79.1, R87.2, R89.2, R92.1, R99.1, R100.1, R103.2, R105.2, R111.2, R112.1, S1.2, S2.2, S3.1, S4.MP (A), S5.2, U1.7 (VSS), U1.9 (D14), U1.11 (E), U1.13 (F), U2.4 (2Y3), U2.6 (~E), U2.7 (VEE), U2.8 (GND), U2.11 (1Y3), U3.4 (VSS), U4.4 (GND), U5.47 (VREG_PGND), U5.61 (GND), U6.2 (GND), U7.2 (GND), U8.2 (V_{SS}), U9.2 (V_{SS}), U10.2 (V_{SS}), U11.2 (V_{SS}), U12.2 (GND), U12.6 (GND), U12.27 (GND), U12.40 (GND), U12.45 (GND), U12.49 (EP), U13.19 (TESTEN), U13.57 (GND), U14.4 (GND), U15.2 (PGND), U15.11 (GND), U15.15 (PGND), U16.4 (V-), U17.4 (AGND), Y1.2, Y1.4, Y2.2 (GND), Y2.4 (GND), Y3.2, Y3.4
GPIO25: R22.2, U5.37 (GPIO25)
unnamed: C2.1, R6.2
unnamed: C7.1, R16.2, Y1.3
unnamed: C23.1, R38.2
unnamed: C75.1, R84.2, Y3.3
unnamed: C78.2, R93.2
unnamed: C79.2, R94.2
unnamed: C80.2, R95.2
unnamed: C83.2, R98.2
unnamed: C85.1, R96.1, U16.7
unnamed: C86.1, R97.1, U16.1
unnamed: C90.1, R102.1, R106.2, R109.1
unnamed: C91.1, R104.1, R107.2, R108.1
unnamed: C92.1, C93.1, R110.1
unnamed: D3.1 (K), J17.18 (+5V)
unnamed: J4.2, R5.2
unnamed: J10.2, R9.2
unnamed: J11.3 (D1+), R10.2
unnamed: J11.2 (D1-), R11.2
unnamed: J11.7 (D2+), R12.2
unnamed: J11.6 (D2-), R13.2
unnamed: J13.4 (CC1), R39.2
unnamed: J13.10 (CC2), R40.2
unnamed: J13.5 (DN2), J13.7 (DN1), R46.2
unnamed: J13.6 (DP1), J13.8 (DP2), R47.2
unnamed: J13.13 (SHIELD), R44.1
unnamed: J14.4 (CC1), R41.2
unnamed: J14.10 (CC2), R42.2
unnamed: J14.5 (DN2), J14.7 (DN1), R48.2
unnamed: J14.6 (DP1), J14.8 (DP2), R49.2
unnamed: J14.13 (SHIELD), R45.1
unnamed: LD1.2 (A), R22.1
unnamed: LD2.2 (A), R43.1
unnamed: LD3.2 (A), R86.1
unnamed: Q1.1 (G), R52.2
unnamed: Q2.1 (G), R53.2
unnamed: Q3.1 (G), R62.2
unnamed: Q4.1 (G), R63.2
unnamed: R25.2, R26.2, R33.2, R38.1
unnamed: R27.2, R33.1, R34.2
unnamed: R28.2, R34.1, R35.2
unnamed: R29.2, R35.1, R36.2
unnamed: R30.2, R36.1, R37.2
unnamed: R31.2, R32.2, R37.1
unnamed: R46.1, U6.1 (I/O1)
unnamed: R47.1, U6.3 (I/O2)
unnamed: R48.1, U7.1 (I/O1)
unnamed: R49.1, U7.3 (I/O2)
unnamed: R85.2, S5.1
unnamed: J13.2 (VBUS), J13.11 (VBUS), S4.2 (B)
unnamed: R6.1, R7.2, U1.1 (A)
unnamed: R8.1, U1.3 (B)
unnamed: U1.4 (H=*B), U1.5 (C)
unnamed: R7.1, R8.2, U1.2 (G-*A)
unnamed: R17.1, R18.2, U4.1 (~CS)
unnamed: R24.2, U5.51 (USB_DM)
unnamed: R23.2, U5.52 (USB_DP)
unnamed: C49.1, C51.1, U12.37 (REFP)
unnamed: C42.1, C43.1, U12.31 (REFQ0)
unnamed: C44.1, C45.1, U12.32 (REFQ1)
unnamed: C52.1, U12.42 (SOG/Y)
unnamed: R79.2, U12.13 (SWREF1k)
unnamed: C55.1, U12.25 (XTI), Y2.1 (OSC)
unnamed: C50.1, U12.26 (XTO), Y2.3 (OSC)
unnamed: R83.2, U13.46 (USB_DM)
unnamed: R82.2, U13.47 (USB_DP)
unnamed: C63.1, C64.1, C65.1, U13.23 (DVDD), U13.45 (VREG_VOUT), U13.50 (DVDD)
unnamed: R93.1, U15.7 (INL)
unnamed: R98.1, U15.10 (INR)
unnamed: C82.1, U15.8 (VREF)
unnamed: C81.2, R91.1, R92.2, U16.3 (+), U16.5 (+)
unnamed: R95.1, R97.2, U16.2 (-)
unnamed: R94.1, R96.2, U16.6 (-)
unnamed: C96.1, U17.7 (FLT)
unnamed: C92.2, C93.2, C94.1, C95.1, U17.5 (VA)
VBUS: C3.1, C4.1, C5.2, C25.2, C26.2, C27.2, C28.2, C29.2, C30.2, C31.2, C32.2, C41.1, C84.2, C87.2, C88.1, C89.1, D3.2 (A), FB1.1, J1.1, J3.3, J4.6, J10.6, J11.1 (VBUS1), J11.5 (VBUS2), J15.4, J18.2, JP1.10, JP1.15, JP1.16, R56.1, R57.1, R64.1, R65.1, R73.2, R74.2, R80.2, R81.2, R91.2, R101.1, R110.2, U2.16 (VCC), U6.5 (VBUS), U7.5 (VBUS), U8.1 (V_{IN}), U8.3 (CE), U9.1 (V_{IN}), U9.3 (CE), U10.1 (V_{IN}), U10.3 (CE), U11.1 (V_{IN}), U11.3 (CE), U15.4 (PVDD), U15.5 (MUTE), U15.6 (VDD), U15.13 (PVDD), U16.8 (V+)
